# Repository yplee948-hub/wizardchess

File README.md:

# Wizard Chess

A Harry Potter-style physical chess board that moves pieces autonomously using an electromagnet on a CoreXY gantry. Players interact via voice command or a web UI — the board physically slides the pieces to match the move.

## How It Works

```
Browser (Next.js UI)
        │
        │  WebSocket (LAN)
        ▼
ESP32-S3 (control_firmware)   ◄──── I2S Microphone (voice → Whisper)
        │
        │  UART @ 115200
        ▼
Raspberry Pi Pico (motor_firmware)
        │
        ▼
CoreXY gantry + Electromagnet
```

1. A player speaks a move ("e2 to e4") or clicks it in the UI.
2. The **ESP32-S3** transcribes voice via OpenAI Whisper (or receives it over WebSocket) and forwards it to the Pico.
3. The **Pico** validates the move, plans the physical path, and drives the CoreXY stepper motors and electromagnet to move the piece.
4. Game state lives on the Pico and is relayed back to the UI in real time.

## Repository Structure

```
wizardchess/
├── motor_firmware/      # Raspberry Pi Pico — CoreXY motion + chess game logic
├── control_firmware/    # Seeed XIAO ESP32-S3 — voice + WebSocket bridge (ESP-NOW to motor)
├── UI/                  # Next.js web UI + WebSocket broker (only copy — do not duplicate)
├── prints/              # KiCad PCB + gerbers (STLs on OneDrive)
└── README.md            # This file
```

> **Web UI:** Use the `UI/` folder only. If you download a separate “web interface” zip, merge into `UI/` or replace it — do not add a second top-level copy.

## Hardware Required

| Component | Role |
|-----------|------|
| Raspberry Pi Pico (RP2040) | Motor control + game logic |
| Seeed XIAO ESP32-S3 | Voice recognition + Wi-Fi bridge |
| 2× Stepper motors (+ driver) | CoreXY X/Y motion |
| Electromagnet (H-bridge driven) | Piece pickup |
| ICS-43432 I2S microphone | Voice input |
| Custom motor PCB | Integrates Pico + drivers |

## Quick Start

See the README in each subdirectory for full setup instructions:

- [`motor_firmware/`](motor_firmware/README.md) — flash the Pico first
- [`control_firmware/`](control_firmware/README.md) — flash the ESP32-S3 second
- [`UI/`](UI/README.md) — run the web interface last
## Fabrication Files (Prints)

STL models, resin slicer files (.ctb), KiCad PCB, laser cut SVGs, and Fusion 360 source files are stored on OneDrive (too large for git):

**[Open OneDrive folder](https://uwnetid-my.sharepoint.com/:f:/r/personal/ktaing_uw_edu/Documents/wizard_chess?csf=1&web=1&e=kmWmI7)**

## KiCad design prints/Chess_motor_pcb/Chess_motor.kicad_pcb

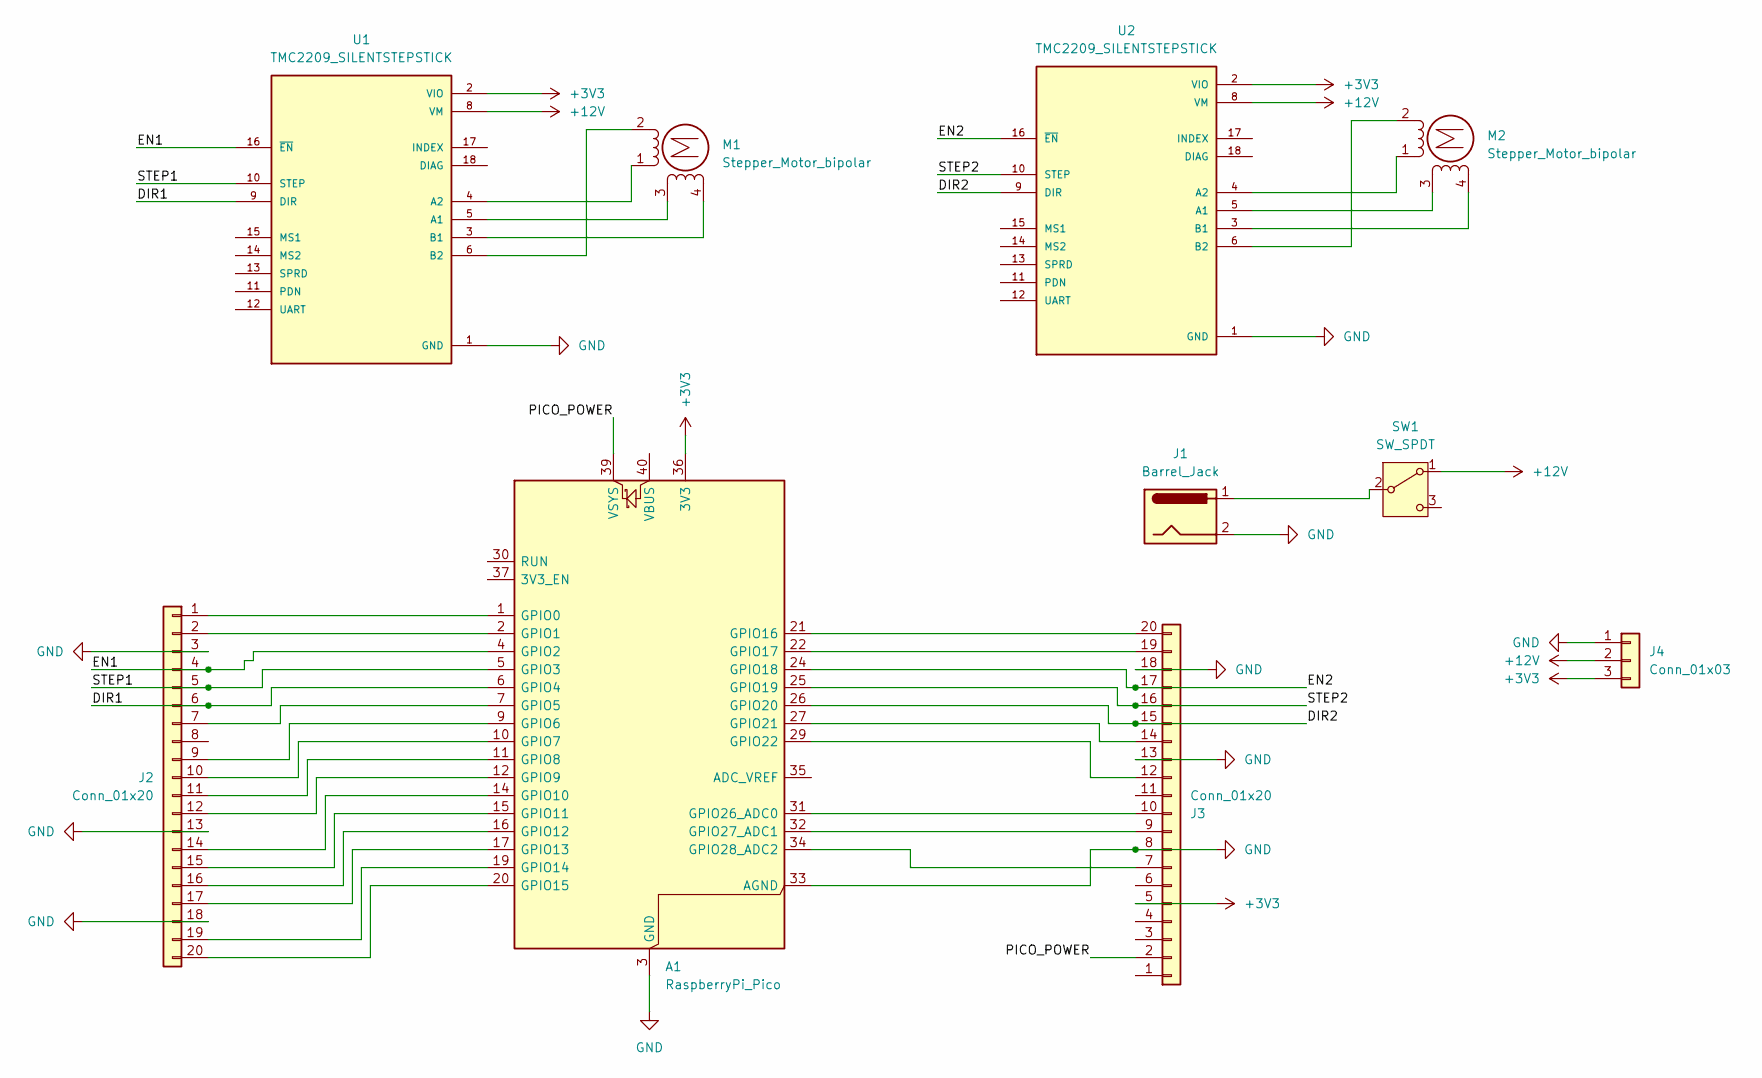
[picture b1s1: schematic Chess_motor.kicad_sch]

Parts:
A1: RaspberryPi_Pico; RaspberryPi_Pico_Common_THT
J1: Barrel_Jack; BarrelJack_Horizontal
J2, J3: Conn_01x20; PinHeader_1x20_P2.54mm_Vertical
J4: Conn_01x03; PinHeader_1x03_P2.54mm_Vertical
M1, M2: Stepper_Motor_bipolar; PinHeader_1x04_P2.54mm_Vertical
SW1: SW_SPDT; SW_Slide-03_Wuerth-WS-SLTV_10x2.5x6.4_P2.54mm
U1, U2: TMC2209_SILENTSTEPSTICK; MODULE_TMC2209_SILENTSTEPSTICK; PARTREV 1.20

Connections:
+3V3: A1.36 (3V3), J3.5, J4.3, U1.2 (VIO), U2.2 (VIO)
+12V: J4.2, SW1.1 (A), U1.8 (VM), U2.8 (VM)
/DIR1: A1.6 (GPIO4), J2.6, U1.9 (DIR)
/DIR2: A1.26 (GPIO20), J3.15, U2.9 (DIR)
/EN1: A1.4 (GPIO2), J2.4, U1.16 (~EN)
/EN2: A1.24 (GPIO18), J3.17, U2.16 (~EN)
/PICO_POWER: A1.39 (VSYS), J3.2
/STEP1: A1.5 (GPIO3), J2.5, U1.10 (STEP)
/STEP2: A1.25 (GPIO19), J3.16, U2.10 (STEP)
GND: A1.3 (GND), A1.8 (GND), A1.13 (GND), A1.18 (GND), A1.23 (GND), A1.28 (GND), A1.33 (AGND), A1.38 (GND), J1.2, J2.3, J2.13, J2.18, J3.8, J3.13, J3.18, J4.1, U1.1 (GND), U1.7 (GND), U2.1 (GND), U2.7 (GND)
unnamed: A1.1 (GPIO0), J2.1
unnamed: A1.2 (GPIO1), J2.2
unnamed: A1.7 (GPIO5), J2.7
unnamed: A1.9 (GPIO6), J2.9
unnamed: A1.10 (GPIO7), J2.10
unnamed: A1.11 (GPIO8), J2.11
unnamed: A1.12 (GPIO9), J2.12
unnamed: A1.14 (GPIO10), J2.14
unnamed: A1.15 (GPIO11), J2.15
unnamed: A1.16 (GPIO12), J2.16
unnamed: A1.17 (GPIO13), J2.17
unnamed: A1.19 (GPIO14), J2.19
unnamed: A1.20 (GPIO15), J2.20
unnamed: A1.21 (GPIO16), J3.20
unnamed: A1.22 (GPIO17), J3.19
unnamed: A1.27 (GPIO21), J3.14
unnamed: A1.29 (GPIO22), J3.12
unnamed: A1.31 (GPIO26_ADC0), J3.10
unnamed: A1.32 (GPIO27_ADC1), J3.9
unnamed: A1.34 (GPIO28_ADC2), J3.7
unnamed: M1.2 (-), U1.6 (B2)
unnamed: M2.2 (-), U2.6 (B2)
unnamed: J1.1, SW1.2 (B)
unnamed: M1.3, U1.5 (A1)
unnamed: M1.1, U1.4 (A2)
unnamed: M1.4, U1.3 (B1)
unnamed: M2.3, U2.5 (A1)
unnamed: M2.1, U2.4 (A2)
unnamed: M2.4, U2.3 (B1)

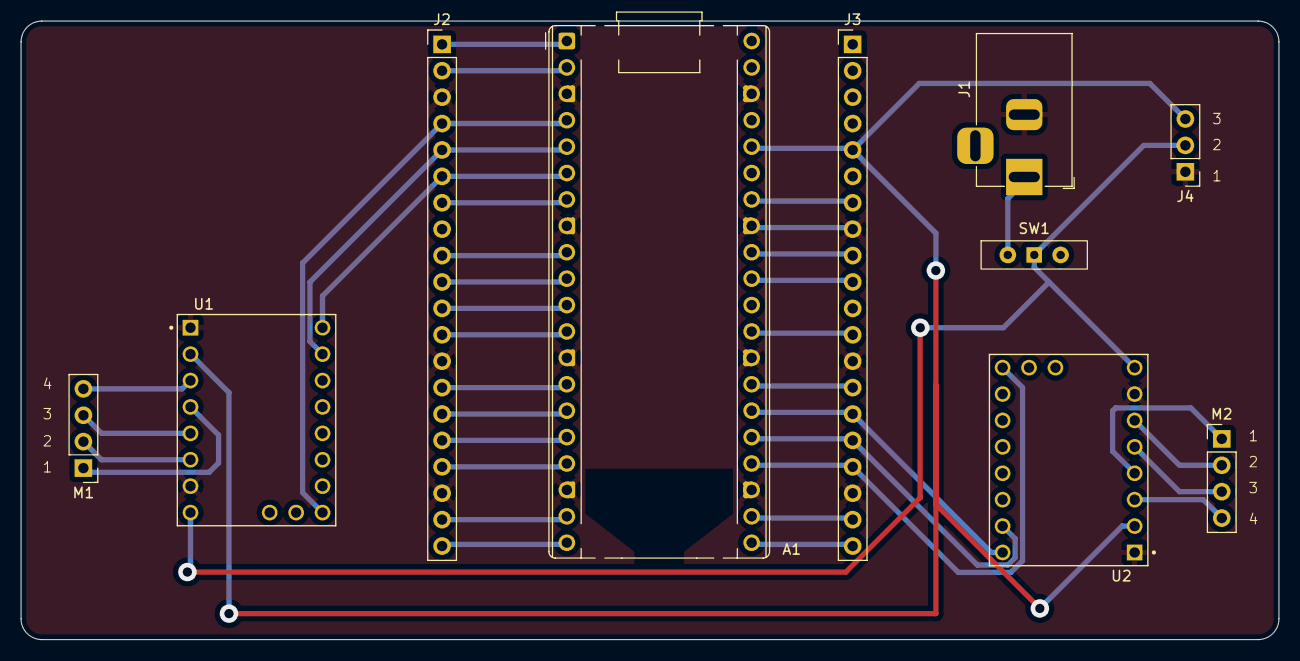
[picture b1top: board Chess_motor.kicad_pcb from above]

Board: 2 copper layers, 121.0 x 59.5 mm, 10 parts (0 on the bottom side), 39 nets.

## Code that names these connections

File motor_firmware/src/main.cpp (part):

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#include "Electromagnet.h"
#include "ChessGame.h"
#include "MovePlanner.h"
#include "NullSerial.h"  // disables Serial — magnet shares UART0 pins (GPIO1/3)

// ---- pins (ESP32 DevKit GPIO numbers) ----
// Constructor arg order: StepperMotor(EN, STEP, DIR), Electromagnet(IN1, IN2, ENA).
// Stepper 1 (TMC2209): EN=GPIO23, STEP=GPIO32, DIR=GPIO33
// Stepper 2 (TMC2209): EN=GPIO2,  STEP=GPIO5,  DIR=GPIO4
//   GPIO2 strapping, idles LOW; TMC2209 EN active-low so LOW = enabled (safe at boot).
//   GPIO5 strapping, safe as output.
StepperMotor motorA(23, 32, 33);
StepperMotor motorB(2, 5, 4);
CoreXY xy(motorA, motorB);

// Magnet H-bridge (L298N): IN1=GPIO3, IN2=GPIO15, ENA=GPIO1.
//   ⚠️ ENA=GPIO1 (U0TXD), IN1=GPIO3 (U0RXD) are the UART0 console pins, so
//   Serial is disabled board-wide via NullSerial.h to keep it off the magnet.
//   GPIO1 needs a 10k pull-down (magnet off at boot); GPIO15 strapping idles HIGH.
Electromagnet magnet(3, 15, 1);
static constexpr bool MAGNET_ENABLED = true;

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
